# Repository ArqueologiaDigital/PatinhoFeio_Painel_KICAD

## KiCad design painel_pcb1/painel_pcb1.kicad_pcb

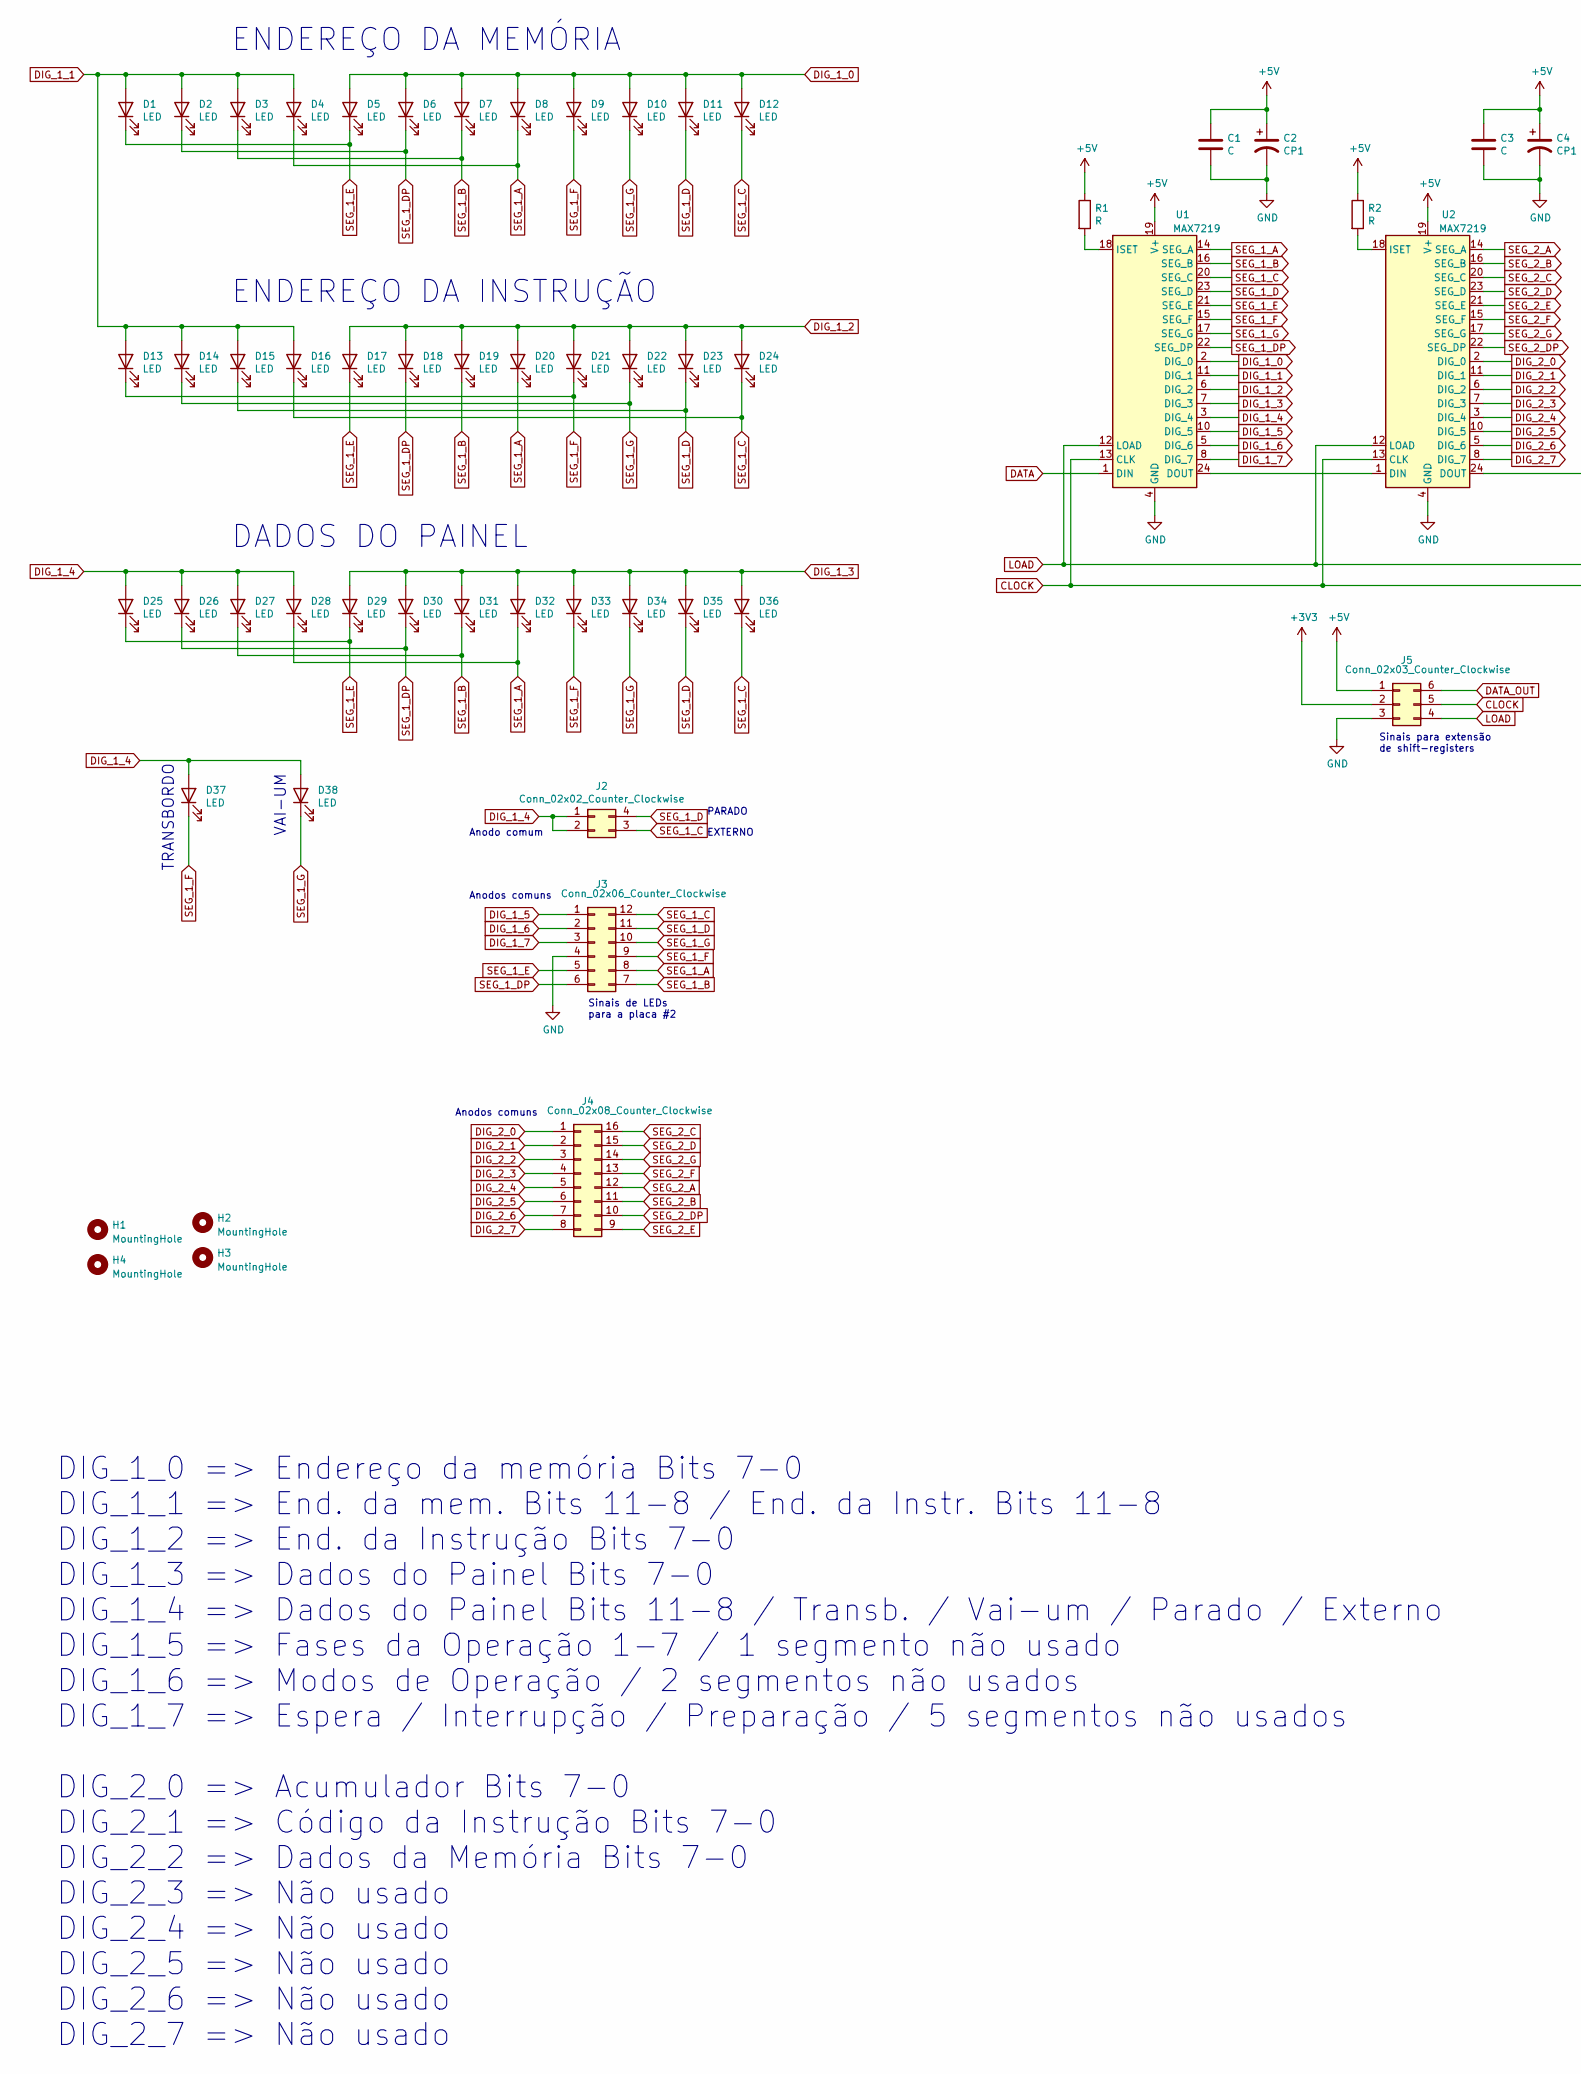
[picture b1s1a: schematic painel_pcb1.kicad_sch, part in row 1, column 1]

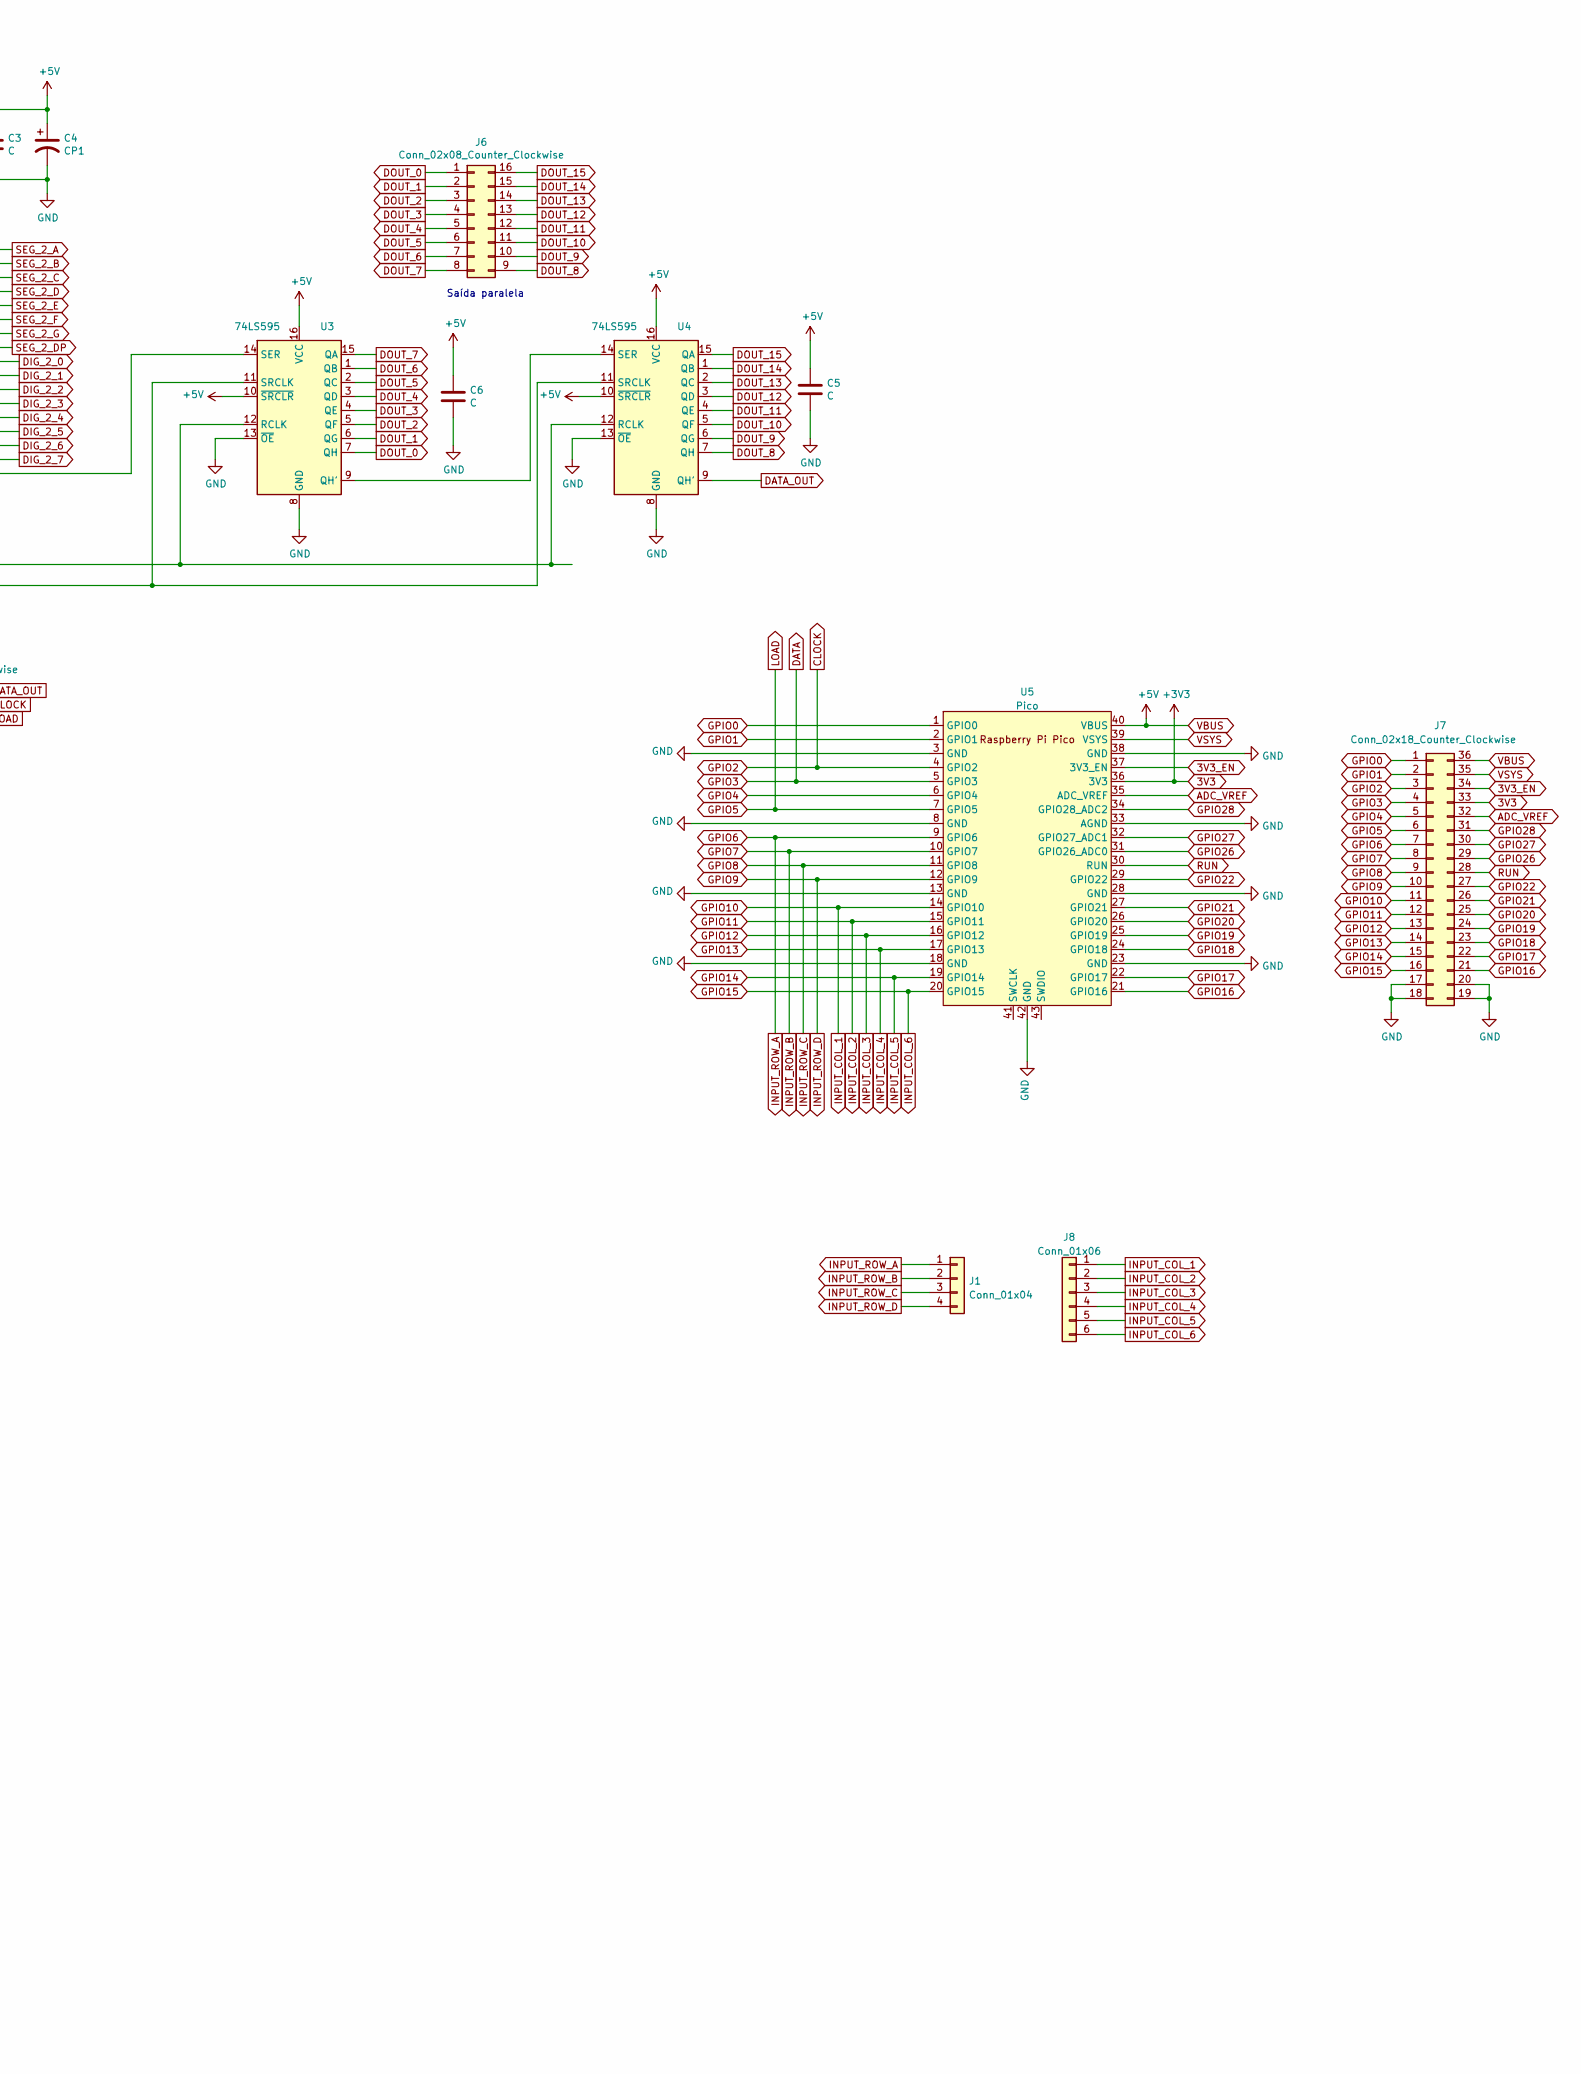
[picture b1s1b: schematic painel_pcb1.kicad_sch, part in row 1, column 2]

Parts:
C1, C3, C5, C6: C; C_Disc_D5.0mm_W2.5mm_P2.50mm
C2, C4: CP1; CP_Radial_D4.0mm_P2.00mm
D1, D2, D3, D4, D5, D6, D7, D8, D9, D10, D11, D12, D13, D14, D15, D16, D17, D18, D19, D20, D21, D22, D23, D24, D25, D26, D27, D28, D29, D30, D31, D32, D33, D34, D35, D36, D37, D38: LED; LED_D3.0mm
H1, H2, H3, H4: MountingHole; MountingHole_3.2mm_M3
J1: Conn_01x04; PinHeader_1x04_P2.54mm_Vertical
J2: Conn_02x02_Counter_Clockwise; PinHeader_2x02_P2.54mm_Vertical
J3: Conn_02x06_Counter_Clockwise; PinHeader_2x06_P2.54mm_Vertical
J4, J6: Conn_02x08_Counter_Clockwise; PinHeader_2x08_P2.54mm_Vertical
J5: Conn_02x03_Counter_Clockwise; PinHeader_2x03_P2.54mm_Vertical
J7: Conn_02x18_Counter_Clockwise; PinHeader_2x18_P2.54mm_Vertical
J8: Conn_01x06; PinHeader_1x06_P2.54mm_Vertical
R1, R2: R; R_Axial_DIN0207_L6.3mm_D2.5mm_P10.16mm_Horizontal
U1, U2: MAX7219; DIP-24_W7.62mm_Socket_LongPads
U3, U4: 74LS595; DIP-16_W7.62mm_LongPads
U5: Pico; RPi_Pico_SMD_TH

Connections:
3V3: J5.2, J7.33, U5.36 (3V3)
3V3_EN: J7.34, U5.37 (3V3_EN)
ADC_VREF: J7.32, U5.35 (ADC_VREF)
CLOCK: J5.5, J7.3, U1.13 (CLK), U2.13 (CLK), U3.11 (SRCLK), U4.11 (SRCLK), U5.4 (GPIO2)
DATA: J7.4, U1.1 (DIN), U5.5 (GPIO3)
DATA_OUT: J5.6, U4.9 (QH')
DIG_1_0: D5.2 (A), D6.2 (A), D7.2 (A), D8.2 (A), D9.2 (A), D10.2 (A), D11.2 (A), D12.2 (A), U1.2 (DIG_0)
DIG_1_1: D1.2 (A), D2.2 (A), D3.2 (A), D4.2 (A), D13.2 (A), D14.2 (A), D15.2 (A), D16.2 (A), U1.11 (DIG_1)
DIG_1_2: D17.2 (A), D18.2 (A), D19.2 (A), D20.2 (A), D21.2 (A), D22.2 (A), D23.2 (A), D24.2 (A), U1.6 (DIG_2)
DIG_1_3: D29.2 (A), D30.2 (A), D31.2 (A), D32.2 (A), D33.2 (A), D34.2 (A), D35.2 (A), D36.2 (A), U1.7 (DIG_3)
DIG_1_4: D25.2 (A), D26.2 (A), D27.2 (A), D28.2 (A), D37.2 (A), D38.2 (A), J2.1, J2.2, U1.3 (DIG_4)
DIG_1_5: J3.1, U1.10 (DIG_5)
DIG_1_6: J3.2, U1.5 (DIG_6)
DIG_1_7: J3.3, U1.8 (DIG_7)
DIG_2_0: J4.1, U2.2 (DIG_0)
DIG_2_1: J4.2, U2.11 (DIG_1)
DIG_2_2: J4.3, U2.6 (DIG_2)
DIG_2_3: J4.4, U2.7 (DIG_3)
DIG_2_4: J4.5, U2.3 (DIG_4)
DIG_2_5: J4.6, U2.10 (DIG_5)
DIG_2_6: J4.7, U2.5 (DIG_6)
DIG_2_7: J4.8, U2.8 (DIG_7)
DOUT_0: J6.1, U3.7 (QH)
DOUT_1: J6.2, U3.6 (QG)
DOUT_2: J6.3, U3.5 (QF)
DOUT_3: J6.4, U3.4 (QE)
DOUT_4: J6.5, U3.3 (QD)
DOUT_5: J6.6, U3.2 (QC)
DOUT_6: J6.7, U3.1 (QB)
DOUT_7: J6.8, U3.15 (QA)
DOUT_8: J6.9, U4.7 (QH)
DOUT_9: J6.10, U4.6 (QG)
DOUT_10: J6.11, U4.5 (QF)
DOUT_11: J6.12, U4.4 (QE)
DOUT_12: J6.13, U4.3 (QD)
DOUT_13: J6.14, U4.2 (QC)
DOUT_14: J6.15, U4.1 (QB)
DOUT_15: J6.16, U4.15 (QA)
GND: C1.2, C2.2, C3.2, C4.2, C5.2, C6.2, J3.4, J5.3, J7.17, J7.18, J7.19, J7.20, U1.4 (GND), U1.9 (GND), U2.4 (GND), U2.9 (GND), U3.8 (GND), U3.13 (~OE), U4.8 (GND), U4.13 (~OE), U5.3 (GND), U5.8 (GND), U5.13 (GND), U5.18 (GND), U5.23 (GND), U5.28 (GND), U5.33 (AGND), U5.38 (GND), U5.42 (GND)
GPIO0: J7.1, U5.1 (GPIO0)
GPIO1: J7.2, U5.2 (GPIO1)
GPIO4: J7.5, U5.6 (GPIO4)
GPIO5: J5.4, J7.6, U1.12 (LOAD), U2.12 (LOAD), U3.12 (RCLK), U4.12 (RCLK), U5.7 (GPIO5)
GPIO6: J1.1, J7.7, U5.9 (GPIO6)
GPIO7: J1.2, J7.8, U5.10 (GPIO7)
GPIO8: J1.3, J7.9, U5.11 (GPIO8)
GPIO9: J1.4, J7.10, U5.12 (GPIO9)
GPIO10: J7.11, J8.1, U5.14 (GPIO10)
GPIO11: J7.12, J8.2, U5.15 (GPIO11)
GPIO12: J7.13, J8.3, U5.16 (GPIO12)
GPIO13: J7.14, J8.4, U5.17 (GPIO13)
GPIO14: J7.15, J8.5, U5.19 (GPIO14)
GPIO15: J7.16, J8.6, U5.20 (GPIO15)
GPIO16: J7.21, U5.21 (GPIO16)
GPIO17: J7.22, U5.22 (GPIO17)
GPIO18: J7.23, U5.24 (GPIO18)
GPIO19: J7.24, U5.25 (GPIO19)
GPIO20: J7.25, U5.26 (GPIO20)
GPIO21: J7.26, U5.27 (GPIO21)
GPIO22: J7.27, U5.29 (GPIO22)
GPIO26: J7.29, U5.31 (GPIO26_ADC0)
GPIO27: J7.30, U5.32 (GPIO27_ADC1)
GPIO28: J7.31, U5.34 (GPIO28_ADC2)
unnamed: R1.2, U1.18 (ISET)
unnamed: R2.2, U2.18 (ISET)
unnamed: U1.24 (DOUT), U2.1 (DIN)
unnamed: U2.24 (DOUT), U3.14 (SER)
unnamed: U3.9 (QH'), U4.14 (SER)
RUN: J7.28, U5.30 (RUN)
SEG_1_A: D4.1 (K), D8.1 (K), D20.1 (K), D28.1 (K), D32.1 (K), J3.8, U1.14 (SEG_A)
SEG_1_B: D3.1 (K), D7.1 (K), D19.1 (K), D27.1 (K), D31.1 (K), J3.7, U1.16 (SEG_B)
SEG_1_C: D12.1 (K), D16.1 (K), D24.1 (K), D36.1 (K), J2.3, J3.12, U1.20 (SEG_C)
SEG_1_D: D11.1 (K), D15.1 (K), D23.1 (K), D35.1 (K), J2.4, J3.11, U1.23 (SEG_D)
SEG_1_DP: D2.1 (K), D6.1 (K), D18.1 (K), D26.1 (K), D30.1 (K), J3.6, U1.22 (SEG_DP)
SEG_1_E: D1.1 (K), D5.1 (K), D17.1 (K), D25.1 (K), D29.1 (K), J3.5, U1.21 (SEG_E)
SEG_1_F: D9.1 (K), D13.1 (K), D21.1 (K), D33.1 (K), D37.1 (K), J3.9, U1.15 (SEG_F)
SEG_1_G: D10.1 (K), D14.1 (K), D22.1 (K), D34.1 (K), D38.1 (K), J3.10, U1.17 (SEG_G)
SEG_2_A: J4.12, U2.14 (SEG_A)
SEG_2_B: J4.11, U2.16 (SEG_B)
SEG_2_C: J4.16, U2.20 (SEG_C)
SEG_2_D: J4.15, U2.23 (SEG_D)
SEG_2_DP: J4.10, U2.22 (SEG_DP)
SEG_2_E: J4.9, U2.21 (SEG_E)
SEG_2_F: J4.13, U2.15 (SEG_F)
SEG_2_G: J4.14, U2.17 (SEG_G)
VBUS: C1.1, C2.1, C3.1, C4.1, C5.1, C6.1, J5.1, J7.36, R1.1, R2.1, U1.19 (V+), U2.19 (V+), U3.10 (~SRCLR), U3.16 (VCC), U4.10 (~SRCLR), U4.16 (VCC), U5.40 (VBUS)
VSYS: J7.35, U5.39 (VSYS)

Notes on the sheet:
Saída paralela
EXTERNO
ENDEREÇO DA INSTRUÇÃO
TRANSBORDO
Anodos comuns
PARADO
DIG_1_0 => Endereço da memória Bits 7-0 DIG_1_1 => End. da mem. Bits 11-8 / End. da Instr. Bits 11-8 DIG_1_2 => End. da Instrução Bits 7-0 DIG_1_3 => Dados do Painel Bits 7-0 DIG_1_4 => Dados do Painel Bits 11-8 / Transb. / Vai-um / Parado / Externo DIG_1_5 => Fases da Operação 1-7 / 1 segmento não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
VAI-UM
DADOS DO PAINEL
ENDEREÇO DA MEMÓRIA
Sinais de LEDs para a placa #2
Anodo comum
Sinais para extensão de shift-registers

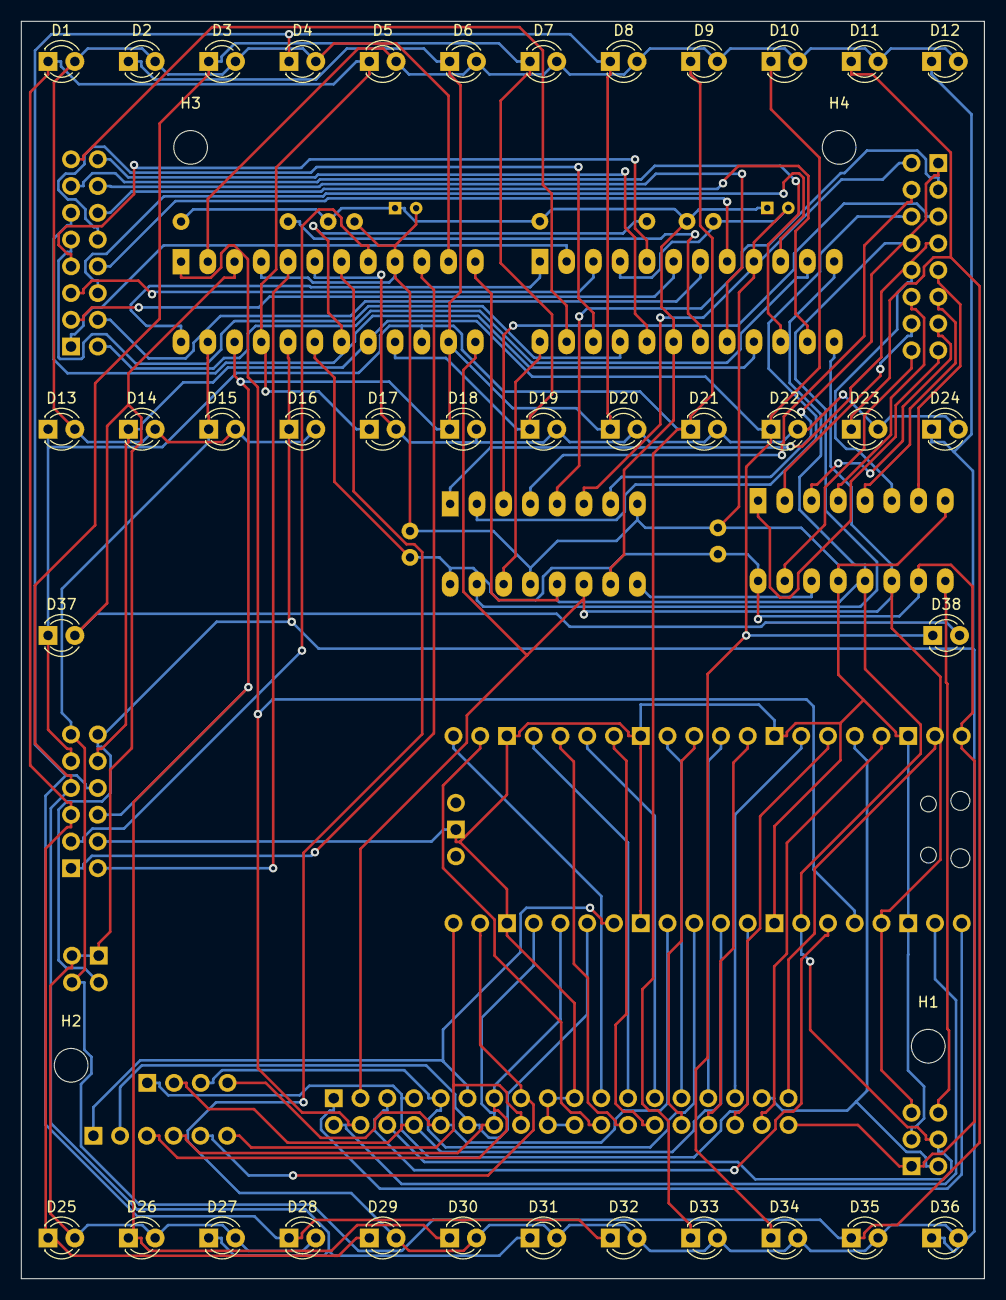
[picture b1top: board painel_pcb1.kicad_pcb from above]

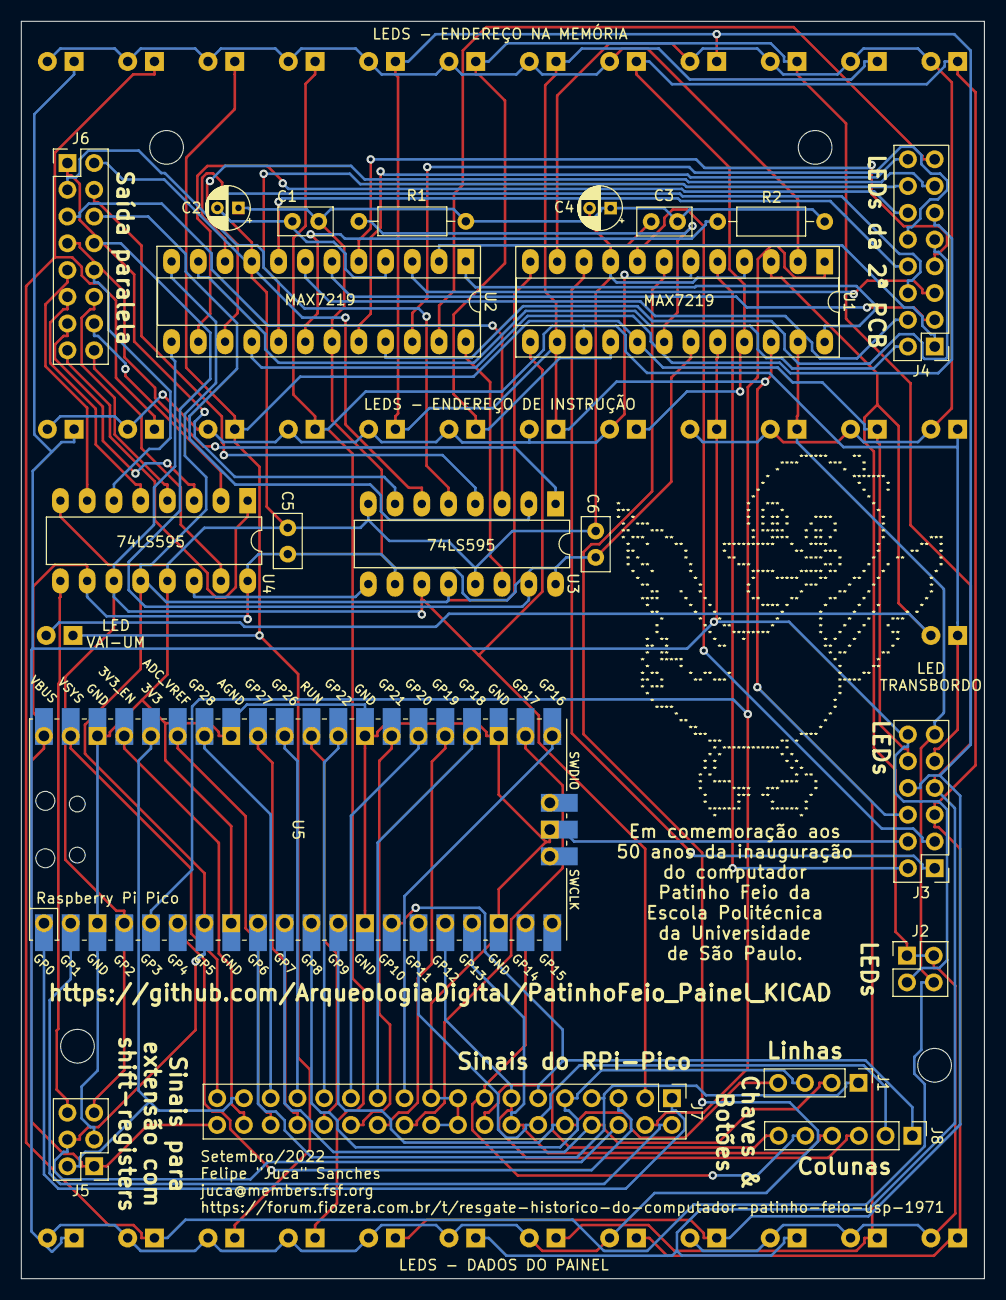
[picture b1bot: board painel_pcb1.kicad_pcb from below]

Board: 2 copper layers, 91.4 x 119.4 mm, 63 parts (21 on the bottom side), 87 nets.

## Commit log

2022-07-28 WIP: PCBs pro Painel do Patinho Feio (iniciadas no KICAD 5, mas vou tentar migrar pro KICAD 6 pra poder usar as RP Pico Libs)
2022-07-28 converted to KICAD 6
2022-09-10 autorouting
2022-09-10 Eu acho que essa versão da PCB tá quase boa pra mandar rodar
